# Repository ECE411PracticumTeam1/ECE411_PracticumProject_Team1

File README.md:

# ECE411-Practicum Project
This is the repository for our programmable keyboard macropad. It houses all our schematics, case and pcb designs, code, and documentations.

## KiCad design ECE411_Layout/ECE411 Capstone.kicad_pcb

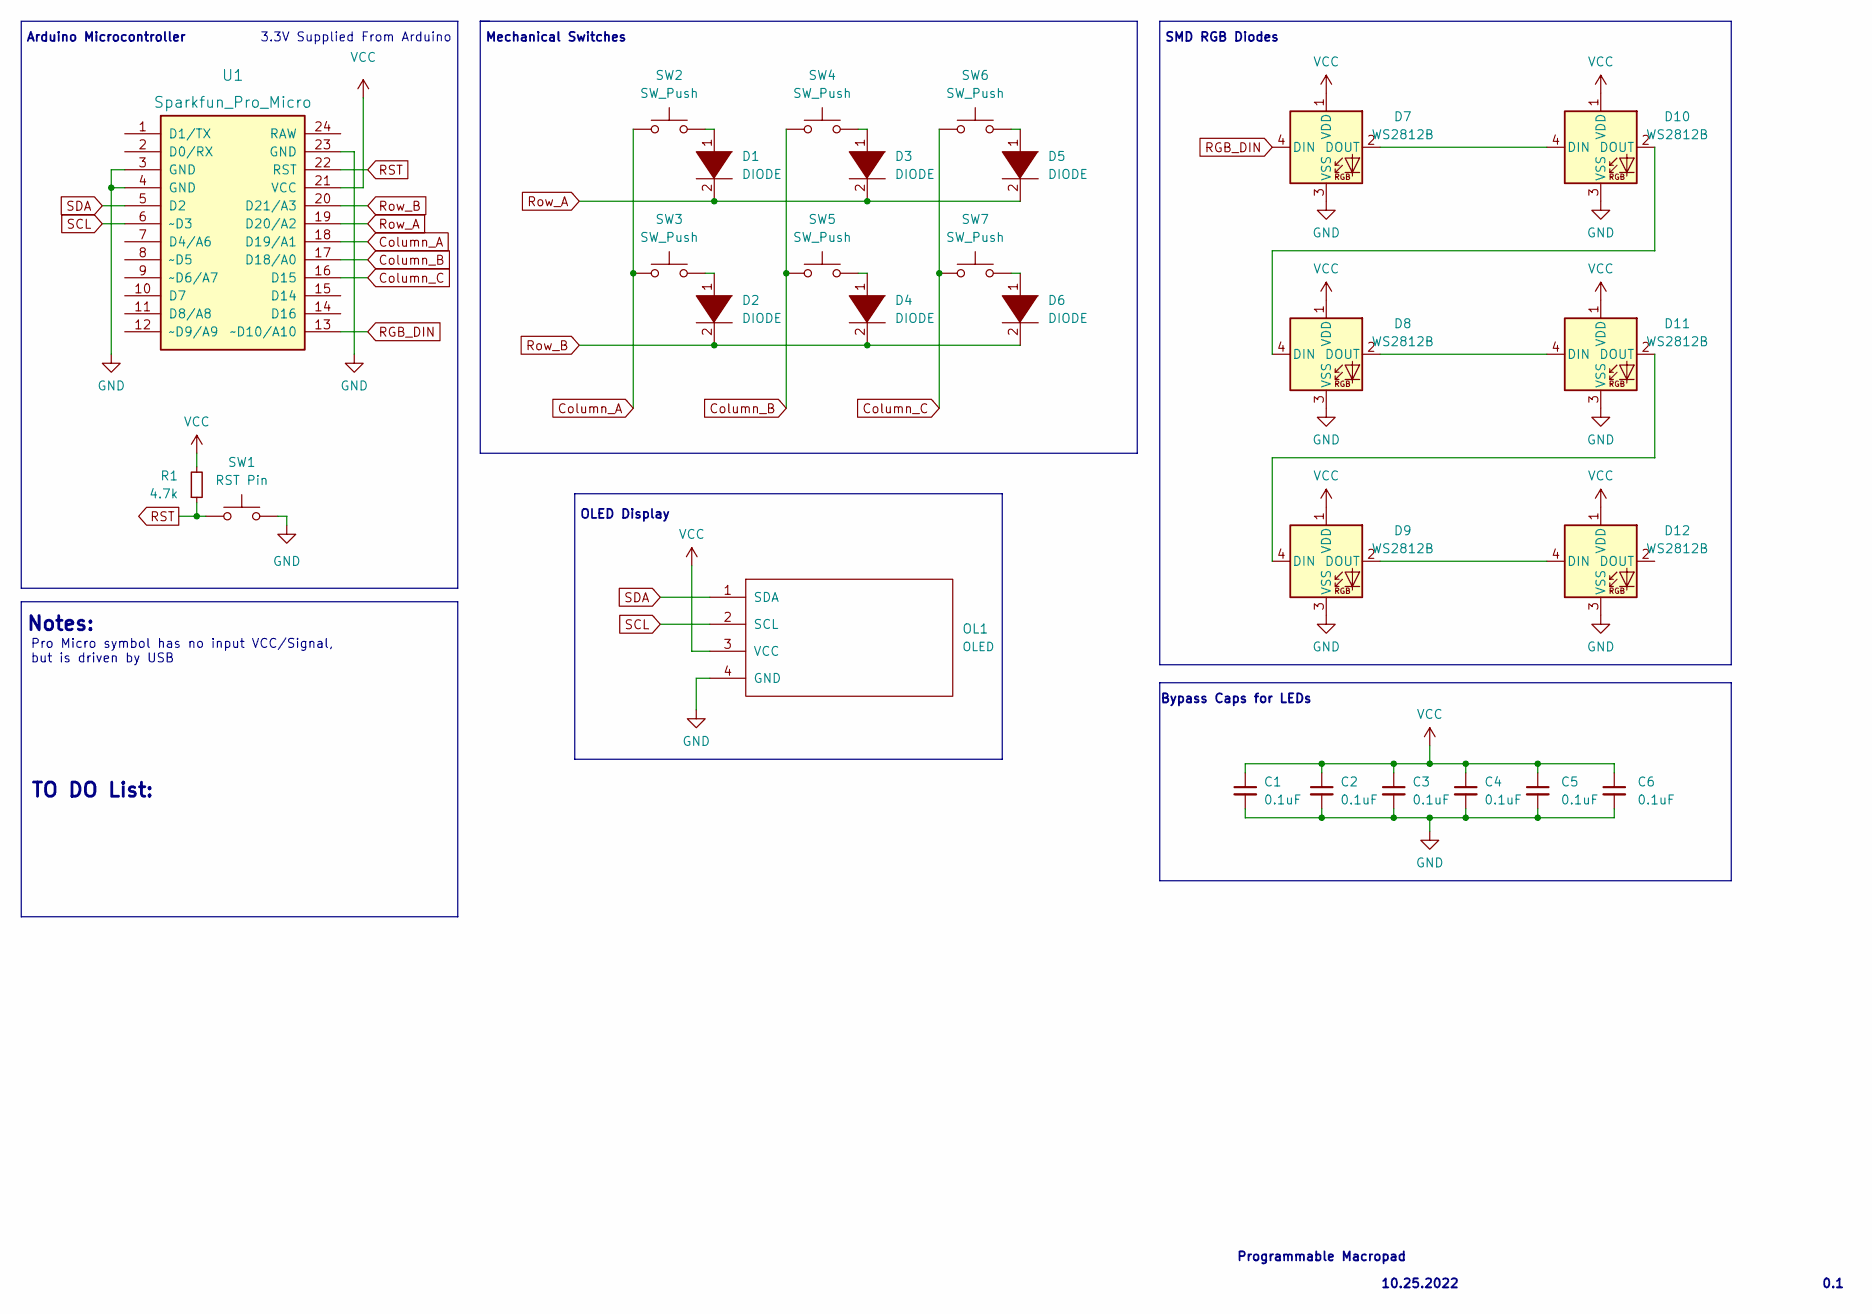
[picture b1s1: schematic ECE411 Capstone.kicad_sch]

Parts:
C1, C2, C3, C4, C5, C6: 0.1uF; C_0805_2012Metric
D1, D2, D3, D4, D5, D6: DIODE; D_SOD-123
D7, D8, D9, D10, D11, D12: WS2812B; LED_WS2812B_PLCC4_5.0x5.0mm_P3.2mm
OL1: OLED; OLED_v2
R1: 4.7k; R_0201_0603Metric
SW1: RST Pin; SW_Push_1P1T_NO_6x6mm_H9.5mm
SW2, SW3, SW4, SW5, SW6, SW7: SW_Push; MXOnly-1U-NoLED
U1: Sparkfun_Pro_Micro; ProMicro_v3

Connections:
Column_A: SW2.1, SW3.1, U1.18 (D19/A1)
Column_B: SW4.1, SW5.1, U1.17 (D18/A0)
Column_C: SW6.1, SW7.1, U1.16 (D15)
GND: C1.2, C2.2, C3.2, C4.2, C5.2, C6.2, D7.3 (VSS), D8.3 (VSS), D9.3 (VSS), D10.3 (VSS), D11.3 (VSS), D12.3 (VSS), OL1.4 (GND), SW1.2, U1.3 (GND), U1.4 (GND), U1.23 (GND)
unnamed: D1.1 (K), SW2.2
unnamed: D2.1 (K), SW3.2
unnamed: D3.1 (K), SW4.2
unnamed: D4.1 (K), SW5.2
unnamed: D5.1 (K), SW6.2
unnamed: D6.1 (K), SW7.2
unnamed: D8.4 (DIN), D10.2 (DOUT)
unnamed: D7.2 (DOUT), D10.4 (DIN)
unnamed: D9.4 (DIN), D11.2 (DOUT)
unnamed: D8.2 (DOUT), D11.4 (DIN)
unnamed: D9.2 (DOUT), D12.4 (DIN)
RGB_DIN: D7.4 (DIN), U1.13 (~D10/A10)
RST: R1.1, SW1.1, U1.22 (RST)
Row_A: D1.2 (A), D3.2 (A), D5.2 (A), U1.19 (D20/A2)
Row_B: D2.2 (A), D4.2 (A), D6.2 (A), U1.20 (D21/A3)
SCL: OL1.2 (SCL), U1.6 (~D3)
SDA: OL1.1 (SDA), U1.5 (D2)
VCC: C1.1, C2.1, C3.1, C4.1, C5.1, C6.1, D7.1 (VDD), D8.1 (VDD), D9.1 (VDD), D10.1 (VDD), D11.1 (VDD), D12.1 (VDD), OL1.3 (VCC), R1.2, U1.21 (VCC)

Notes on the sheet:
0.1
Mechanical Switches
OLED Display
3.3V Supplied From Arduino
10.25.2022
Arduino Microcontroller
Bypass Caps for LEDs
Notes:
TO DO List:
Programmable Macropad
Pro Micro symbol has no input VCC/Signal, but is driven by USB
SMD RGB Diodes

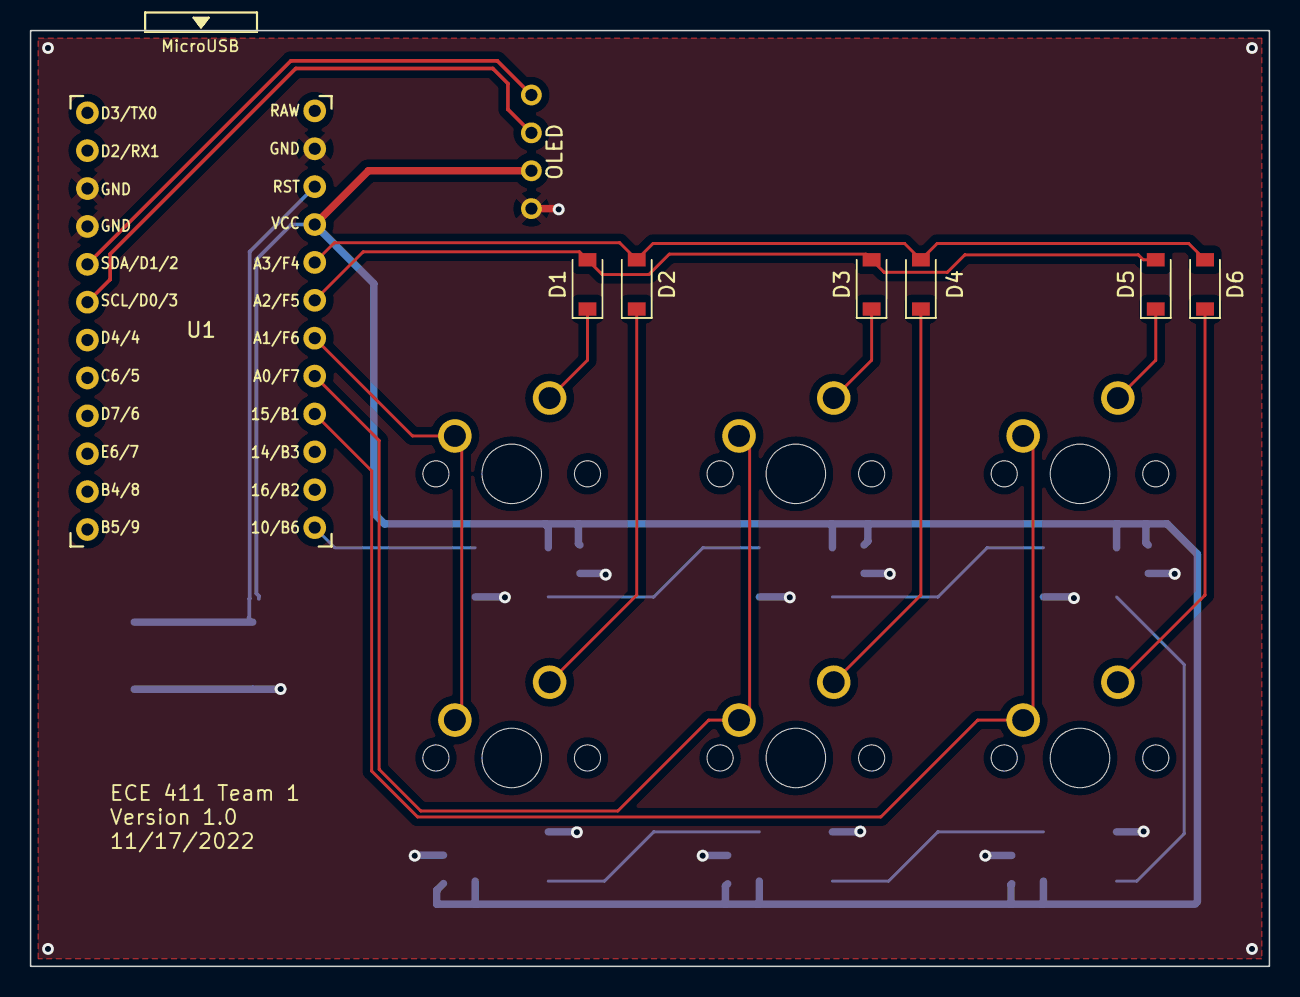
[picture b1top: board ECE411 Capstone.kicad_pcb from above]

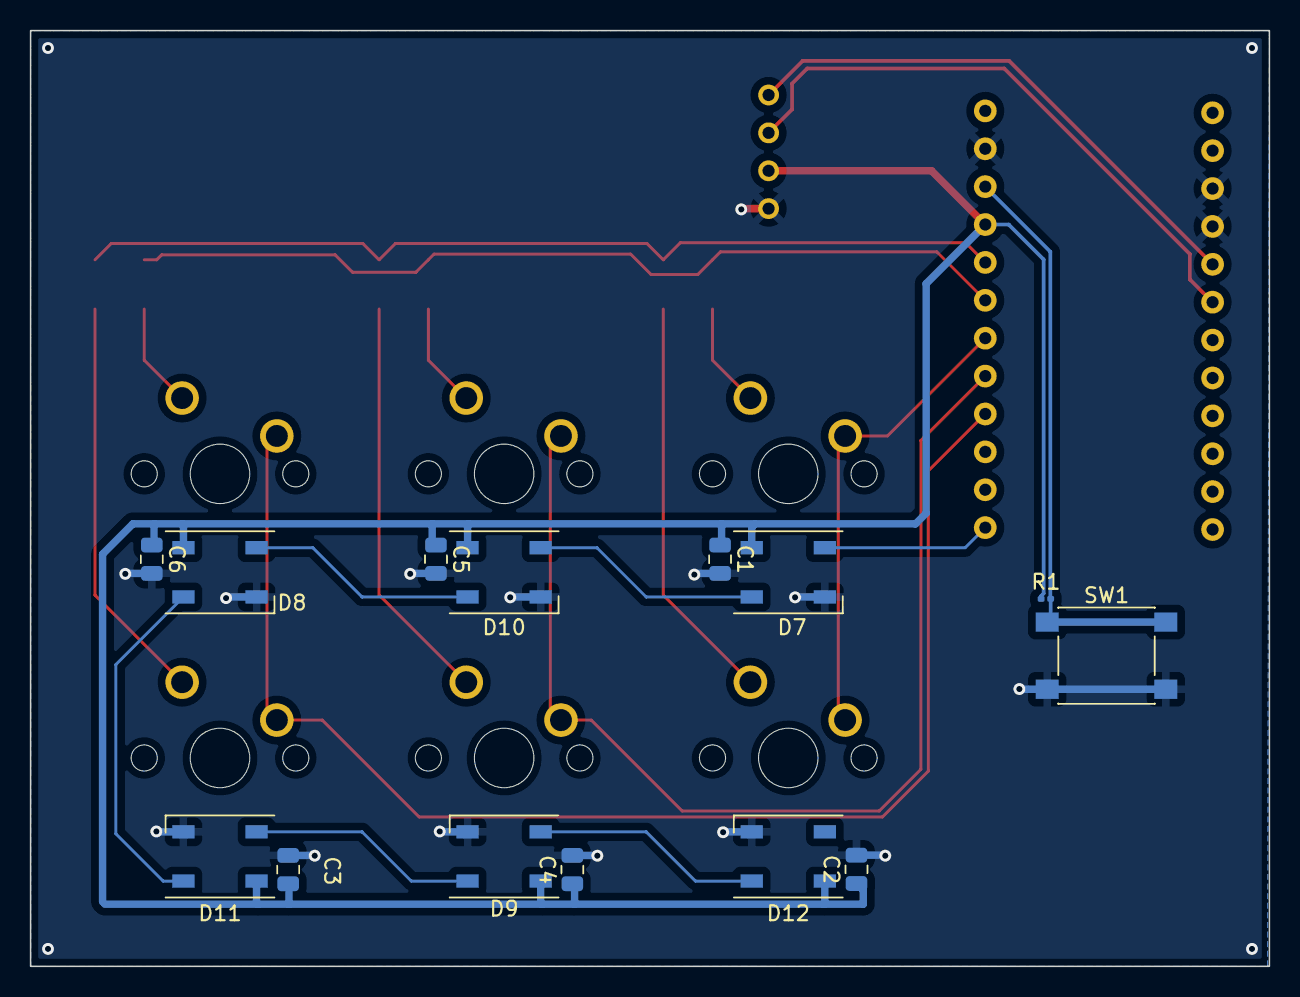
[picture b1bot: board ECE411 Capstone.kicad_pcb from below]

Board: 2 copper layers, 83.1 x 62.7 mm, 28 parts (14 on the bottom side), 22 nets.

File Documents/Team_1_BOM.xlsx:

Bill Of Materials for: [TEAM 1] [Team D3onathon]
Last modified: [11/9/2022]
PCB version: 1.0
BOM revision: A |  | P/NP | Place/Not Place (components marked NP are not stuffed on the board)
Count | Part References | P/NP | Mfg | Mfg PN | Description | Dist | Dist Part Number | Cost Ea. | Cost Total
30.0 | C1, C2, C3, C4, C5, C6 | P | KEMET | C0402C104K4PAC7867 | 0.1uF Ceramic Capacitor | Digikey | 399-C0402C104K4PAC7867TR-ND | 0.1 | 3
100.0 | D1, D2, D3, D4, D5, D6 | P | Bridgold | bg-195 | DIODE | Amazon | B09TKVYJL6 | 0.08 | 8
20.0 | D7, D8, D9, D10, D11, D12 | P | DIYmall | WS2812B | LEDs | Amazon | B0B1MC997K | 0.4 | 8
5.0 | OL1 | P | Frienda | Frienda-d'Affichage-02 | OLED | Amazon | B08CDN5PSJ | 3.5 | 17.5
50.0 | R1 | P | YAGEO | RT0603FRE134K7L | 4.7k Chip Resistor | Digikey | 13-RT0603FRE134K7LTR-ND | 0.059 | 2.95
10.0 | SW1 | P | Omron Electronics Inc-EMC | B3F-1020 | RST Pin | Digikey | SW402-ND | 0.38 | 3.8
70.0 | SW2, SW3, SW4, SW5, SW6, SW7 | P | N\C | N/A | SW_Push | Amazon | B09JSM1911 | 0.34 | 23.8
1.0 | U1 | P | Sparkfun | DEV-12640 | Sparkfun_Pro_Micro | Sparkfun | DEV-12640 | 19.5 | 19.5
 |  |  |  |  |  |  |  | TOTAL: | 86.55
VERSION INFO
Rev | Date | Notes
A | 44874.0 | Intial BOM, with Rough Draft CAD

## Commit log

2022-10-23 Inital testing of qmk firmware
2022-10-27 Project Schematic Ver.0.1
2022-10-27 Renamed schematic files
2022-10-27 Schematic Version 0.2
2022-11-01 Team 1 Gannt Chart
2022-11-01 Capstone Schematic + Initial PCB
2022-11-03 Functional Prototype
2022-11-03 Update Prototype Summary
2022-11-03 PCB + Schematic
2022-11-07 Added keyboard firmware configuration
2022-11-07 Added keyboard firmware for flashing
2022-11-10 BOM
    Revision A
2022-11-10 Added Function Decomposition Diagrams
2022-11-10 Updated PCB Layout + Routes
2022-11-10 Removed unused files
2022-11-14 Updated Schematic + PCB for review
2022-11-17 Final CAD layout
2022-11-29 Updated firmware with AltF4 and Windows search + bongo cat
2022-12-01 Update for testing final version
    *Removed define for 128x64 OLED
    *Added defines for RGB LEDs
2022-12-01 Update for testing final board
    *Updated diode_direction to ROW2COL
    *Updated matrix pins
2022-12-01 Update for testing final board
    Enabled RGB LEDs
2022-12-08 Added & updated directories + updated names of files
2022-12-08 Added images for wiki
2022-12-08 Removed some images
2022-12-08 Added case design files
